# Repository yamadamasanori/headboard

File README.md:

# ヘッドボードLED コントローラ（ESP32-S3）

ベッドのヘッドボードに付けた LED を、Home Assistant から操作するための ESP32 ファームウェアと、ブラウザ用の書き込み・設定ページです。

- 読書灯とバックライトの 2 系統を、PWM でそれぞれ独立に調光（0〜255、なめらかにフェード）
- MQTT で Home Assistant から操作。MQTT 自動探索（discovery）に対応しているので、接続すると自動で「ライト」が 2 つ追加される。ブローカーには TLS（MQTTS）でも接続できる
- 量産向けに、USB では設定を変えられない。Wi-Fi はスマホから Bluetooth で、MQTT・Tailscale・GPIO などは Wi-Fi に繋がった本体の設定ページ（`http://headboard-xxxxxx.local/`）で設定する
- 本体の設定ページでは、動作ログ・前回の再起動の理由と直前のエラーも見られ、ファームウェアの更新（OTA）もできる。更新に失敗したら前の版に自動で戻る
- 最初のファームウェアの書き込みは、USB で繋いだパソコンのブラウザから行う（ESP Web Tools を同梱）
- 基板上のフルカラー LED で、Wi-Fi・Tailscale・MQTT の接続状態を色で表示。OLED ディスプレイ（SSD1306、128×64）をつなげば、文字でも表示（Seeed Studio XIAO ESP32S3 版は OLED で表示）
- Home Assistant から本体の状態（電波の強さ・再起動の理由・エラー・メモリ・温度など）と、ライトの点灯時間・消費電力・電力量を見られる。再起動やファームウェアの更新も Home Assistant から行える
- ESP32 自身が Tailscale で tailnet に参加し、離れた場所の Home Assistant の MQTT ブローカーにも VPN 経由で接続できる（[MicroLink](https://github.com/CamM2325/microlink) を組み込み）

## ファイル構成

| パス | 内容 |
|---|---|
| `main/` | ファームウェアのソース（ESP-IDF / C） |
| `main/Kconfig.projbuild` | ビルド時の設定（ボード、開発用に USB から設定できるようにするか、Home Assistant からの更新に使う配布元の URL） |
| `main/board.h` | ボードごとの違い（GPIO の既定値、配布するファイル名など） |
| `main/status_led.c`、`main/status_oled.c` | 状態表示（N16R8 のフルカラー LED、OLED）。表示する状態の判定は `main/status.c` で共通 |
| `main/oled_font.c` | OLED 用のフォント（X11 misc-fixed、パブリックドメイン。`tools/gen_font.py` で作る） |
| `components/mdns/` | mDNS（Espressif、Apache-2.0、mdns-v1.15.1 を同梱。`headboard-xxxxxx.local` の名前で本体を開くため） |
| `partitions.csv` | フラッシュの区画（N16R8 用。ファームウェア 4MB × 2 の OTA 構成と、クラッシュの記録 256KB） |
| `partitions_8mb.csv` | フラッシュ 8MB 用の区画（XIAO 用。ファームウェア 3.75MB × 2 と、クラッシュの記録 256KB） |
| `components/microlink/` | Tailscale クライアント MicroLink（MIT、コミット 1cb8d1c を同梱。中継（DERP）の地域が違う相手に送る変更あり、`VERSION` 参照） |
| `sdkconfig.defaults*` | ビルド設定（共通 / ESP32-S3 用 / ボードごと（`.n16r8`、`.xiao`）） |
| `keys/headboard-signing-pubkey.pem` | ファームウェアの署名を確かめる公開鍵（秘密鍵はリポジトリに入れない。「ファームウェアの署名」参照） |
| `web/index.html` | 書き込み・設定ページ。本体にも組み込まれ、本体の設定ページとしても使われる |
| `web/firmware/headboard-led-ota.bin` | ビルド済みファームウェア（ESP32-S3 用のアプリ。USB での書き込みと、本体の設定ページからの更新の両方に使う） |
| `web/firmware/headboard-led-boot.bin`, `headboard-led-otadata.bin` | USB で書き込むときに一緒に書き込むブートローダーとパーティション表、起動するアプリの選択（設定の保存領域には書き込まない） |
| `web/manifest.json` | ESP Web Tools 用の定義 |
| `web/xiao/` | XIAO ESP32S3 用の `manifest.json` と `firmware/headboard-led-xiao-*.bin`（ファイルの役割は N16R8 用と同じ） |
| `web/vendor/esp-web-tools/` | ESP Web Tools 10.4.0（Apache-2.0）。CDN に頼らずオフラインでも動くよう同梱 |
| `web/vendor/qrcode-generator/` | QR Code Generator 2.0.4（MIT）。本体ラベルの QR コード用 |
| `tools/serve.py` | 設定ページをローカルで開くための簡易サーバー |
| `.devcontainer/` | VS Code の devcontainer 設定（ESP-IDF v5.3.1 のイメージを使用） |
| `tools/build.sh` | ESP-IDF 環境でビルド・署名して `web/` を更新（docker は使わない。署名用の秘密鍵が必要） |
| `tools/package_web.py` | ビルド結果を `web/firmware/`（XIAO 用は `web/xiao/firmware/`）にまとめ、ライセンス表示を `web/` にコピーする |
| `tools/gen_font.py` | OLED 用のフォントを BDF から C の配列にする |
| `.github/workflows/pages.yml` | GitHub に置いた場合に、`web/` を GitHub Pages に公開する設定（ビルドはせず、ファームウェアの署名を確かめてから公開） |
| `platformio.ini` | PlatformIO でビルドする場合の設定 |
| `LICENSE` | このプロジェクトのライセンス（MIT） |
| `THIRD_PARTY_NOTICES.md` | 同梱・組み込みしている第三者のソフトウェアのライセンス |
| `web/LICENSE.txt`、`web/THIRD_PARTY_NOTICES.txt` | 上の 2 つのコピー（設定ページからリンク。`tools/package_web.py` が作成） |

## 基板と配線（既定値）

次の 2 種類のボードに対応しています。ファームウェアはボードごとに別です（書き込みページでボードを選びます）。

- ESP32-S3-DevKitC-1 互換の ESP32-S3 N16R8 基板（フラッシュ 16MB、オクタル PSRAM 8MB）。状態表示は基板上のフルカラー LED
- Seeed Studio XIAO ESP32S3（フラッシュ 8MB、オクタル PSRAM 8MB）。状態表示は、つないだ OLED ディスプレイ（SSD1306、128×64、I2C）。フラッシュ 16MB の XIAO ESP32S3 Plus でも、XIAO 用のファームウェアが動きます（8MB だけを使います）

### ESP32-S3 N16R8

| 用途 | 既定の GPIO |
|---|---|
| 読書灯 | GPIO4 |
| バックライト | GPIO5 |
| 状態表示 LED（基板上の WS2812） | GPIO48 |
| OLED の SDA・SCL（任意） | 使わない（つなぐときの例: GPIO8・GPIO9） |

OLED ディスプレイ（SSD1306）もつなげます。3.3V・GND・SCL・SDA の 4 本でつなぎ、設定ページの「状態表示」で SDA と SCL の GPIO を入れて保存します。フルカラー LED と OLED の両方に表示します（表示の内容は「[状態表示（OLED）](#状態表示oled)」）。起動時の動作に関わる GPIO0・3・45・46 と、使用中の GPIO48・4・5 は避けてください。

GPIO は設定ページから変更できます。フラッシュと PSRAM が使う GPIO26〜37、USB 端子の GPIO19・20、COM 端子の GPIO43・44 は選べません。
ESP32 のピンで LED を直接駆動することはできないので、ロジックレベル N チャネル MOSFET などのドライバを挟んでください。ドライバがアクティブ Low の回路なら、設定ページの「出力を反転する」をオンにします。PWM 周波数の既定は 5 kHz（13 bit 分解能。周波数を下げると最大 14 bit）です。

明るさ（1〜255）は、設定ページの「最小デューティ比」（明るさ 1）から「最大デューティ比」（明るさ 255）までを対数で割り振ります。1 段ごとに同じ割合で明るくなるので、目で見た変化がほぼ均等になります（照明の調光規格 DALI と同じ考え方。既定の 0.1〜100% では 1 段で約 2.8%、明るさ 50% で約 3%）。暗いときにちらつくなら最小を上げ、明るい側で変化がなくなるなら最大を下げて、回路に合わせてください。

LED 電球などに入っている定電流ドライバ（入力に電解コンデンサとコイルがある小さな基板）を、電源ごと PWM でオン・オフするつなぎ方は、調光に向きません。コンデンサで平らにされて明るい側で変化がなくなり、暗い側ではドライバが止まったり動いたりしてちらつきます。LED に直列に電流制限の抵抗を入れて MOSFET で駆動するか、PWM 調光の入力（DIM 端子）があるドライバを使ってください。

基板の USB-C 端子は 2 つとも使えます。

- **COM 端子**（USB シリアル変換チップ経由）: 書き込み・状態表示・ラベル表示ができ、動作ログも出ます
- **USB 端子**（ESP32-S3 内蔵の USB）: 書き込み・状態表示・ラベル表示ができます。ログは出ません

基板の BOOT ボタン（GPIO0）は、動作中に長押しすると次のように働きます。

| 押す長さ | 動作 | 状態表示 LED |
|---|---|---|
| 3 秒以上 | Wi-Fi の設定だけを消して再起動し、Bluetooth での設定を待つ（MQTT などの設定は残る）。「Tailscale からだけ受け付ける」もオフに戻す | 白・点灯 |
| 10 秒以上 | すべての設定と累計（点灯時間・起動回数など）を消して再起動（工場出荷時の状態） | 赤・点灯 |

LED の色が変わったところで離すと、その動作をします。短く押すと、消えている状態表示を 10 秒間出し直します。

### Seeed Studio XIAO ESP32S3

| 用途 | 既定の GPIO（XIAO のピン） |
|---|---|
| 読書灯（LED1） | GPIO7（D8） |
| バックライト（LED2・LED3） | GPIO44（D7） |
| OLED の SDA | GPIO8（D9） |
| OLED の SCL | GPIO9（D10） |

- OLED は 3.3V・GND・SCL・SDA の 4 本でつなぎます（I2C のアドレスは 0x3C か 0x3D を自動で探します）。OLED の GPIO は、設定ページで変えられます（両方 -1 で使わない）
- 既定の GPIO は専用基板の配線に合わせています
- XIAO の USB-C 端子は ESP32-S3 内蔵の USB です。書き込み・状態表示・ラベル表示ができます。ログは D6（GPIO43、TX）に出るので、見るときは USB シリアル変換器をつないでください（設定ページのログ欄は、本体の設定ページなら Wi-Fi 経由で見られます）
- D7（GPIO44）は COM 端子の RX ですが、XIAO ではバックライトに使うので、COM 端子からの設定の入力は受け付けません（設定は USB-C 端子から）
- D6（GPIO43）はログ用なので選べません。D2（GPIO3）は起動時の動作を決めるピンなので、ライトには使わないでください
- BOOT ボタン（B）の働きは N16R8 と同じです。押している間は、画面に離したときの動作と、押している秒数が出ます
- 基板上のオレンジの LED（GPIO21）は使いません

## 状態表示 LED

| 状態 | 色と光り方 |
|---|---|
| Wi-Fi 未設定（Bluetooth での設定待ち） | 紫・ゆっくり点滅 |
| Wi-Fi 接続中・切断 | 青・速い点滅 |
| Tailscale 接続中（Tailscale を使う場合） | 水色・点滅 |
| MQTT 接続待ち・切断、ブローカー未設定 | 黄・点滅 |
| Tailscale の認証失敗、MQTT の接続拒否（ユーザー名・パスワード違い） | 赤・点滅 |
| すべて正常 | 緑・点灯 → 10 秒後に消灯 |
| Home Assistant からの操作を受信 | 緑・一瞬点滅 |

- 起動直後に白が一瞬点灯します（LED の点灯確認）
- 問題が複数あるときは、Wi-Fi → Tailscale → MQTT の順に、先にある問題を表示します
- 明るさ（既定 32/255）、GPIO（-1 で使わない）、正常時も点灯し続けるかは、設定ページの「状態表示 LED」で変えられます。いま表示している状態は「動作確認」欄にも出ます
- 互換基板には、LED の横に「RGB」と書かれたはんだジャンパがあり、そこをはんだで繋がないと点灯しない製品があります。点灯しないときは確認してください

## 状態表示（OLED）

XIAO ESP32S3 では標準の表示です。N16R8 では、つないで設定したときだけ表示します（フルカラー LED と両方に表示）。

上段（16 ドット）にホスト名と接続状態のアイコン、下段に 1 行 16 文字 × 3 行で状態を英語で表示します。上段の高さを 16 ドットにしているので、上が黄色・下が青の 2 色のモジュールでも、区切りが合います。

```
headboard-a1b2c3  ▂▄▆ [TS][MQ]     ← Wi-Fi の電波の強さ、Tailscale、MQTT
Reading   ON  80%
Backlight OFF
192.168.1.23                        ← Tailscale を使っていれば、tailnet の IP と 3 秒ごとに交互
```

| 状態 | 表示 |
|---|---|
| 起動直後（1 秒） | `Headboard LED`、版、`XIAO ESP32S3` |
| Bluetooth での設定待ち | `Wi-Fi not set` / `Setup via BLE:` / 本体の名前（`PROV_HB_xxxxxx`）。設定用コードは表示しません |
| Wi-Fi 接続中・切断 | `Wi-Fi` / `Connecting...` / SSID |
| Tailscale の認証失敗 | `Tailscale` / `Auth failed (!)` / `Check auth key` |
| Tailscale 接続中 | `Tailscale` / `Connecting...` |
| MQTT の接続拒否 | `MQTT` / `Refused (!)` / `Check user/pass` |
| ブローカー未設定 | `MQTT` / `Not configured` / `Open web setup` |
| MQTT 接続中・切断 | `MQTT` / `Connecting...` / ブローカーのホスト名 |
| すべて正常 | ライトの状態と IP アドレス → 10 秒後に画面を消す |
| BOOT ボタンを押している | `3s: Reset Wi-Fi` / `10s: Reset all` と進み具合 → 3 秒で `Release to: Reset Wi-Fi` → 10 秒で画面全体を反転して `Release to: RESET ALL` |
| 本体を光らせる（Home Assistant） | 画面全体を速く点滅し、`HERE` を大きく表示（10 秒） |

- 上段のアイコンは、繋がっていれば塗りつぶし、接続中は枠だけ、エラーは斜線入りです。Tailscale を使わないときは TS を出しません。下段に tailnet の IP を出している間は、TS の下に線が出ます
- 画面が消えているときも、Home Assistant からライトを操作すると 5 秒（操作したライトの行を 1 秒反転）、BOOT ボタンを短く押すと 10 秒表示します。問題があるときは、消さずに表示し続けます
- 明るさ（既定 32/255）と、正常なときも表示し続けるか、表示を 180° 回すかは、設定ページの「状態表示」で変えられます。明るさは Home Assistant からも変えられ、すぐに反映されます。明るさが 32 未満のときは、OLED の駆動の設定（プリチャージ期間と VCOMH の電圧）を段階的に下げて、さらに暗くします
- 焼き付きを防ぐため、表示を 1 分ごとに 0〜2 ドット横にずらします

## 使い方

量産時の流れは次のとおりです。USB を使うのは 1 の書き込みとラベルの印刷だけで、設定はすべて無線で行います。

1. 未設定のファームウェアを USB で書き込み、本体のラベル（QR コードと設定用コード）を印刷して貼る
2. スマホのアプリ「ESP BLE Provisioning」で QR コードを読み、Wi-Fi を設定する
3. 同じネットワークのパソコンかスマホで本体の設定ページを開き、MQTT などを設定する

### 1. ファームウェアを書き込む（USB）

Web Serial は HTTPS か localhost でしか動かないため、HTML ファイルを直接開かずに、次のどちらかで書き込み用のページを開きます。

- devcontainer の中で `python tools/serve.py` を実行し（8000 番は自動で転送されます）、ホストの Chrome か Edge で http://localhost:8000 を開く
- GitHub のリポジトリに置き、GitHub Pages を有効にする（`.github/workflows/pages.yml` が `web/` を自動で公開します）

基板を USB で繋ぎ、ボード（ESP32-S3 N16R8 か Seeed Studio XIAO ESP32S3）を選んでから「ESP32 に書き込む」を押してシリアルポートを選びます。初回は「消去」を選んでください。
ボードを間違えて N16R8 用を XIAO に書き込むと、「ESP32 に接続」したときに警告が出ます（フラッシュの大きさで判断します）。
COM 端子でポートが表示されないときは、USB シリアル変換チップ（CH340 / CH343 / CP210x）のドライバを入れてください。書き込みが始まらないときは、BOOT ボタンを押したまま RST ボタンを押して離し、書き込みモードにしてから試してください。

2.4.0 からは、USB で書き込んでも設定は消えません（「消去」を選んだときだけ消えます）。2.3.0 までは、USB で書き込むと「消去」を選ばなくても設定が消えていました。

**2.0.0 より前の版から上げるとき:** フラッシュの区画を OTA 用に変えたため、一度だけ USB で「消去」を選んで書き込んでください。それまでの設定は消えるので、設定し直しが必要です。2.0.0 以降は、本体の設定ページから更新できます。

### 2. ラベルを印刷する（USB）

書き込み画面を閉じてから「ESP32 に接続」を押すと、本体の名前（`PROV_HB_xxxxxx`）、設定用コード（8 文字）、本体の設定ページのアドレスと、アプリ用の QR コードが表示されます。「ラベルを印刷」で、この部分だけを印刷できます。

- 設定用コードは本体ごとに決まっていて（チップ固有の ID から作る）、Bluetooth での設定と本体の設定ページのログインに使います。他の人に見せないでください
- ごくまれに固有 ID の無いチップがあり、その場合は初回の起動時に乱数でコードを作って保存します。この場合だけは、工場出荷時に戻してもコードは変わりませんが、フラッシュを消去して書き込むとコードが変わるので、ラベルを貼り直してください
- 量産版のファームウェアは USB から設定を変えられないため、USB の画面には設定の欄が出ません（「状態」「ログ」「点灯テスト」は使えます）

### 3. Wi-Fi を設定する（Bluetooth）

1. スマホに Espressif の公式アプリ「ESP BLE Provisioning」（iOS / Android）を入れます
2. 本体の電源を入れ、状態表示 LED が紫でゆっくり点滅していることを確かめます（Bluetooth での設定待ち）
3. アプリで「Provision New Device」を選び、ラベルの QR コードを読みます。QR が使えないときは、手動で本体の名前（`PROV_HB_xxxxxx`）を選び、設定用コードを入れます
4. 一覧から Wi-Fi を選び、パスワードを入れます。繋がると設定が保存され、Bluetooth は止まります

パスワードの誤りなどで繋がらないときは、アプリにその旨が表示され、そのまま入れ直せます。Wi-Fi を変えたいときは、BOOT ボタンを 3 秒以上押してください。

### 4. 本体の設定ページで設定する（Wi-Fi）

本体と同じネットワークのパソコンかスマホのブラウザで `http://headboard-xxxxxx.local/` を開き（`xxxxxx` はラベルに書かれています）、設定用コードでログインします。`.local` の名前で開けないとき（一部の Android など）は、ルーターの管理画面で本体の IP アドレスを調べて `http://<IP アドレス>/` で開いてください。

MQTT ブローカー（Home Assistant の Mosquitto アドオンなど）のアドレス・ユーザー名・パスワードなどを入力して「保存して再起動」を押します。
パスワード欄は、空欄のまま保存すると以前の値が残ります。「動作確認」のスライダーで、その場で明るさを変えられます。

#### MQTT を TLS で接続する（任意）

ブローカーが TLS（MQTTS、通常は 8883 番）に対応していれば、「MQTT」欄の「TLS で接続する」をオンにします（ポートが 1883 なら 8883 に変わります）。

- ブローカーの証明書を自分で作った（自前の CA で署名した）場合は、「CA 証明書」に CA の証明書（`ca.crt` など、`-----BEGIN CERTIFICATE-----` で始まるもの）の中身を貼り付けます。空欄なら、公開の認証局（Let's Encrypt など）の証明書として確かめます
- 「ブローカーのホスト名 / IP」は、ブローカーの証明書に入っている名前か IP アドレス（subjectAltName）のどれかと同じにしてください。違うと接続しません
- 本体は時計を持たないので、証明書の有効期限は確かめません（期限が切れても繋がります）。期限の前に作り直してください
- Tailscale 経由の接続はもともと暗号化されていますが、TLS をオンにすれば、その場合も同じように証明書を確かめます

- この設定ページは暗号化していない HTTP です。家庭内の LAN で使う前提です（Tailscale 経由で開けば、経路は暗号化されます。Tailscale からだけ開けるようにもできます。「5. Tailscale を使う」参照）
- 設定用コードを 5 回続けて間違えると、1 分間ログインできなくなります

#### ファームウェアの更新（OTA）

本体の設定ページの「ファームウェアの更新」で `web/firmware/headboard-led-ota.bin`（XIAO は `web/xiao/firmware/headboard-led-xiao-ota.bin`）を選んで「更新する」を押します。書き込みが終わると再起動します。

- 新しいファームウェアが起動して Wi-Fi に繋がるまで（Wi-Fi 未設定なら起動するまで）に失敗すると、次の起動で前の版に自動で戻ります
- `headboard-led-boot.bin` などの USB 用のファイルや ESP32-S3 用でないファイル、別のボード用のファイルは、書き込む前に断ります（ボードごとにプロジェクト名を変えて見分けています。2.5.0 以前の N16R8 も、XIAO 用は断ります）
- 2.3.0 からは、正しい鍵で署名したファームウェアだけを書き込みます（Home Assistant からの更新も同じ）。署名がないものや違う鍵のものは、書き込みの最後で断り、今の版のまま動き続けます。2.2.0 以前から 2.3.0 への更新は、まだ署名を確かめない版からなので、そのまま入ります

Home Assistant の「設定 → 更新」からも更新できます（下の「6. Home Assistant で確認する」）。

#### 開発用に USB から設定できるようにする

開発中は、`idf.py menuconfig` の「ヘッドボードLED → USB から設定を変更できるようにする（開発用）」をオンにしてビルドすると、以前の版と同じように USB の設定ページから Wi-Fi・MQTT などを設定できます。量産用のファームウェアでは必ずオフ（既定）にしてください。

### ログの見方と MQTT に繋がらないとき

本体の設定ページ（USB の設定ページでも同じ）の「動作確認」欄は自動で更新され、MQTT に繋がっていないときは、その理由が赤字で表示されます。起動してからの時間、前回の再起動の理由（電源投入・クラッシュ・ウォッチドッグなど）、空きメモリ（内蔵 RAM の今と起動してからの最小値、PSRAM）、直近のエラーと、前回の起動中の最後のエラーも表示されます。

前回の起動がクラッシュで終わったときは、「前回のクラッシュ」にクラッシュの理由・タスク・Backtrace（アドレスの並び）が赤字で表示されます。クラッシュの記録をフラッシュに残しておき、次の起動で読み出すので、シリアルを繋いでいなくても分かります。アドレスは、同じ版をビルドした `build/headboard_led.elf` で関数と行に変換できます（`xtensa-esp32s3-elf-addr2line -pfiaC -e build/headboard_led.elf <アドレス…>`）。

- クラッシュの記録の区画は 2.4.0 で追加しました。2.3.0 以前から本体の設定ページ（Wi-Fi）で更新した本体には区画がないので、一度 USB で書き込んでください（2.4.0 の書き込みページからなら設定は消えません）

| 表示 | 主な原因 |
|---|---|
| 接続を拒否されました: ユーザー名かパスワードが違います / 認証されませんでした | MQTT のユーザー名・パスワード（Home Assistant の Mosquitto アドオンなら、HA のユーザーか、アドオン設定の logins） |
| 接続を断られました / 接続が切られました | ポート番号の誤り（通常は 1883、TLS なら 8883）、ブローカーが動いていない |
| TLS で接続できません | TLS 用でないポート（1883 など）に TLS で繋ごうとしている |
| ブローカーの証明書に「…」が入っていません | ブローカーのホスト名 / IP が、証明書に入っている名前・IP と違う |
| ブローカーの証明書が、設定した CA 証明書で確かめられません | 貼り付けた CA 証明書が、ブローカーの証明書に署名した CA のものでない |
| 応答がありません | IP アドレスの誤り、ファイアウォール、別のネットワーク |
| ホスト名を IP アドレスに変換できません | `homeassistant.local` のような名前は使えないことがあります。IP アドレスで指定してください |
| Tailscale の接続を待っています | Tailscale がオンで、ブローカーにホスト名か tailnet のアドレス（100.64〜100.127）を指定していて、Tailscale がまだ繋がっていない |

ログ欄には次の機能があります。本体の設定ページでは、本体が貯めている起動してからのログ（最大 64KB）を、Wi-Fi 経由でいつでも見られます。USB では COM 端子で接続したときだけ表示されます。前回の起動の最後のログ（2KB、クラッシュの直前など）は「[前回]」を付けて最初に表示します。電源を切ると前回のログは消えます。

- 「一時停止」: 表示を止めます（受信は続き、「再開」でまとめて表示）。ログ欄を上にスクロールしても止まります
- 「直近500行をコピー」: 絞り込み後の最新 500 行をクリップボードにコピーします
- 「ファイルに保存」: 受信した全ログ（最大 20,000 行）をテキストファイルに保存します
- 絞り込み欄（例: `mqtt`、`broker:`）と「警告とエラーだけ」。エラーは赤、警告は黄で表示されます

Tailscale の途中経過のログは、通常は警告以上だけにしています。調べたいときは「デバイス」欄の「詳細ログを出す」をオンにして保存してください。

### 5. Tailscale を使う（任意）

1. Tailscale の管理画面（Settings → Keys）で認証キーを作ります。ESP32 を置きっぱなしにするなら「Reusable」はオフ、期限切れで外れないよう登録後にデバイスの「Disable key expiry」をオンにしておくと安心です
2. 本体の設定ページの「Tailscale」で「tailnet に接続する」をオンにし、認証キーと tailnet 上のホスト名（既定は `headboard-xxxxxx`）を入れて保存します
3. MQTT ブローカーのホスト名に、Home Assistant の tailnet 上の名前（例: `homeassistant`）か tailnet のアドレス（`100.64.x.x`〜`100.127.x.x`）を入れると、Tailscale 経由で接続します。LAN の IP アドレスを入れた場合は、Tailscale の接続を待たずに LAN で直接繋ぎます。`homeassistant.local` のような LAN のホスト名も、Tailscale がオンのときは Tailscale の接続を待ってから繋ぎます（tailnet 上に同じ名前が無ければ、通常の DNS で探します）

「動作確認」欄に Tailscale の状態と VPN の IP アドレスが表示されます。認証キーかホスト名を変えると、次の起動時に鍵を作り直して登録し直します。

#### 本体の設定ページを Tailscale からだけ開けるようにする（任意）

「Tailscale」欄の「本体の設定ページと更新を Tailscale からだけ受け付ける」をオンにすると、LAN から本体の設定ページ・WebSocket・ファームウェアの更新に繋いでも断ります（「Tailscale からだけ開けます」と表示）。設定用コードが漏れても、LAN 内からは設定も更新もできなくなります。

- 先に、Tailscale で `http://<tailnet 上のホスト名>/` を開けることを確かめてからオンにしてください（オンにするときに確認が出ます）
- Tailscale の ACL で、本体に繋げる端末を自分の端末と Home Assistant に絞っておくと、さらに安全です
- tailnet から本体の tailnet の IP に繋いできた接続だけを受け付けます。接続元のアドレスだけでは判断しないので、LAN から接続元を偽っても開けません。2.4.1 からの動作です
- Tailscale に繋がらなくなると、本体の設定ページは開けません（ライト・MQTT・Home Assistant からの更新はそのまま動きます）。戻すには、BOOT ボタンを 3 秒押して Wi-Fi の設定を消し、Bluetooth で設定し直します。これで LAN からも開けるようになります
- Home Assistant のデバイスのページの「デバイスを設定」のリンクは、いつも `http://headboard-xxxxxx.local/`（LAN）を指すので、オンのときは「Tailscale からだけ開けます」と表示されます。Tailscale の `http://<tailnet 上のホスト名>/` から開いてください
- Home Assistant からの更新（GitHub Pages から本体が取りに行く）と、MQTT の接続には関係しません。MQTT も Tailscale 経由にしたいときは、ブローカーに tailnet の名前かアドレスを指定します

### 6. Home Assistant で確認する

Home Assistant に MQTT 統合が設定されていれば、「設定 → デバイスとサービス → MQTT」に、設定ページで付けた名前のデバイスが現れ、「読書灯」と「バックライト」の 2 つのライトが追加されます。明るさとフェード時間（transition）を指定できます。

デバイスのページには、ライトのほかに次のエンティティが追加されます。診断と操作の項目は、デバイスのページの「診断」「設定」欄にまとまり、普段のダッシュボードには出ません。

| 種類 | エンティティ |
|---|---|
| ライトの累計 | 読書灯・バックライトそれぞれの点灯時間、点灯回数、消費電力（推定）、電力量（推定） |
| 診断 | Wi-Fi の電波の強さ・SSID・アクセスポイント・チャンネル、IP アドレス、稼働時間、前回の再起動の理由、前回の再起動が異常か（電圧低下・クラッシュ・ウォッチドッグ）、直前のエラー、前回の起動の最後のエラー、空きメモリ（今と最小値）、内蔵 RAM の空き（今と最小値）、PSRAM の空き、チップの温度、状態表示 LED の表示、起動した回数、電圧低下による再起動の回数、クラッシュによる再起動の回数、Wi-Fi が切れた回数、MQTT の再接続の回数 |
| 診断（Tailscale を使うときだけ） | Tailscale の状態・IP アドレス・ピアの数・認証エラー |
| 操作 | 再起動、本体を光らせる（状態表示 LED が白で 10 秒速く点滅。XIAO は画面が点滅）、更新を確認（配布元の新しい版をすぐに確かめる。配布元を設定したときだけ）、累計をクリア（設定は残る。誤操作を避けるため最初は無効で、使うときはデバイスのページで有効にする）、状態表示 LED の明るさ、状態表示 LED を常に点灯、詳細ログ（XIAO では「画面の明るさ」「画面を常に表示」） |
| 更新 | ファームウェア（新しい版があると「設定 → 更新」に出て、そこから書き込める） |

- 値は 60 秒ごと（と、操作したとき・MQTT に繋がったとき）に送ります
- 消費電力と電力量は、本体の設定ページの「定格消費電力」（既定 1 W）× PWM のデューティ比から計算した推定値です。電力量は Home Assistant の「エネルギー」ダッシュボードに個別のデバイスとして追加できます
- 点灯時間・点灯回数・電力量・起動回数などの累計は、本体に 10 分ごと（と意図した再起動の前）に保存し、再起動しても続きから数えます。電源を急に切ると、最後の保存から後の分（最大 10 分）は残りません
- 累計は工場出荷時に戻すか、設定ページか Home Assistant の「累計をクリア」で 0 に戻ります（「累計をクリア」では設定は残ります）。量産時の検査で増えた分は、出荷前に消してください
- Wi-Fi が切れた回数と MQTT の再接続の回数は、起動してからの回数です（Home Assistant の履歴で長期の傾向を見られます）
- 新しい版は、本体が MQTT につないだときと 6 時間ごと（と HA の「更新を確認」ボタンを押したとき）に配布元（既定は `https://yamadamasanori.github.io/headboard/`、XIAO は `https://yamadamasanori.github.io/headboard/xiao/`。`idf.py menuconfig` の「ヘッドボードLED → ファームウェアの配布元」で変更、空にすると使わない）の `manifest.json` を見て探します。HTTPS でサーバーの証明書を確かめてから取得します。GitHub に push してから Pages に公開され、キャッシュが切れるまで 10 分ほどかかります
- 設定用コード・パスワード・Tailscale の認証キーは MQTT に送りません

## MQTT の仕様

`<id>` は MAC アドレスから作る固有 ID（例: `headboard_a1b2c3`）で、設定ページに表示されます。

| トピック | 向き | 内容 |
|---|---|---|
| `homeassistant/light/<id>/reading/config` など | ESP32 → HA | 自動探索の設定（retain） |
| `headboard/<id>/status` | ESP32 → HA | `online` / `offline`（LWT、retain） |
| `headboard/<id>/reading/set`、`.../backlight/set` | HA → ESP32 | `{"state":"ON","brightness":128,"transition":2}`。`ON` / `OFF` だけでも可 |
| `headboard/<id>/reading/state`、`.../backlight/state` | ESP32 → HA | `{"state":"ON","brightness":128,"color_mode":"brightness"}`（retain） |
| `homeassistant/<sensor など>/<id>/<key>/config` | ESP32 → HA | 診断・累計・操作・更新のエンティティの自動探索の設定（retain）。使わなくなったもの（Tailscale をオフにしたときなど）は空のメッセージで消す |
| `headboard/<id>/diag` | ESP32 → HA | 診断と累計をまとめた JSON（60 秒ごと、retain）。各エンティティは `value_template` でここから値を取り出す |
| `headboard/<id>/update` | ESP32 → HA | `{"installed_version":"2.1.1","latest_version":"2.1.2","release_url":"https://github.com/yamadamasanori/headboard/releases/tag/v2.1.2","in_progress":false,"update_percentage":null}`（retain）。`release_url` は HA の「リリースのお知らせを読む」のリンク |
| `headboard/<id>/restart/set`、`.../identify/set`、`.../check_update/set`、`.../reset_usage/set` | HA → ESP32 | ボタン（内容は何でもよい）。retain 付きのものは無視する |
| `headboard/<id>/sled_brightness/set` | HA → ESP32 | `1`〜`255` |
| `headboard/<id>/sled_always_on/set`、`.../log_verbose/set` | HA → ESP32 | `ON` / `OFF`（本体に保存し、すぐに反映） |
| `headboard/<id>/update/set` | HA → ESP32 | `install` で配布元の新しい版を書き込んで再起動。retain 付きのものは無視する |

ボタンと更新のコマンドは、ブローカーに保持（retain）されていると繋ぐたびに届き、再起動や更新を繰り返してしまうので、retain 付きのものは無視します（ログに `ignored retained command` と出ます）。

Home Assistant が再起動したとき（`homeassistant/status` に `online`）は、自動探索の設定を送り直します。電源投入時はどちらも消灯から始まります。

## 設定コマンド（USB シリアルと WebSocket）

設定ページは、115200 bps のシリアル（USB）か、本体の `ws://headboard-xxxxxx.local/ws`（Wi-Fi）で、1 行 1 コマンドの JSON を送っています。応答は `@@` で始まる 1 行の JSON です（それ以外の行はログ）。WebSocket では最初に `{"cmd":"login","pop":"<設定用コード>"}` でログインします。

```
{"cmd":"hello"}                      機種・バージョン・本体の名前（USB では設定用コードも）
{"cmd":"get"}                        現在の設定（パスワードは「設定済みか」だけ）
{"cmd":"set","config":{...},"reboot":true}   設定を保存（含めた項目だけ変更）
{"cmd":"status"}                     Wi-Fi / MQTT / Tailscale / ライト / 状態表示 LED の状態、空きメモリ（合計・内蔵 RAM の今と最小値・PSRAM）、再起動の理由、エラー、前回のクラッシュ
{"cmd":"prev_log"}                   前回の起動の最後のログ
{"cmd":"light","id":"reading","brightness":100}   点灯テスト
{"cmd":"reset_usage"}                累計（起動回数・点灯時間・電力量など）を 0 に戻す（設定は残す）
{"cmd":"reboot"} / {"cmd":"factory_reset"}
```

量産版（開発用の設定がオフ）では、USB から使えるのは `hello`・`status`・`light`・`prev_log` だけです。

## ビルド

VS Code で「Reopen in Container」を選び、コンテナの中で次を実行します。ESP-IDF v5.3.1 と Python はイメージに入っているので、ホストに ESP-IDF や Python は不要です。docker コマンドは使いません。

```sh
sh tools/build.sh
```

N16R8 用と XIAO 用の両方をビルドし、`web/firmware/`（アプリの `headboard-led-ota.bin` と、USB 用の `headboard-led-boot.bin`・`headboard-led-otadata.bin`）と `web/manifest.json`、`web/xiao/`（同じく `headboard-led-xiao-*.bin` と `manifest.json`）も更新されます。署名用の秘密鍵（`secrets/headboard-signing-key.pem`）がないとビルドできません。`build.sh` は `idf.py set-target` で `sdkconfig`（XIAO は `sdkconfig.xiao`）を作り直すので、`menuconfig` で開発用の設定をオンにしたときは、`build.sh` ではなく次のように実行してください。

```sh
idf.py build && python tools/package_web.py                                    # N16R8
idf.py -B build-xiao -DHB_BOARD=xiao build && python tools/package_web.py build-xiao   # XIAO
```

ボードは `-DHB_BOARD`（既定は `n16r8`）で選びます。ボードごとに `sdkconfig` とビルドのディレクトリを分けてください（XIAO は `sdkconfig.xiao` と `build-xiao`）。混ざるとビルドが止まります。

PlatformIO（`platformio.ini`）の設定は残していますが、動作確認をしていない補助的な経路です。

### ファームウェアの署名

ファームウェアは RSA-3072 の鍵で署名しています（ESP-IDF の「Secure Boot なしの署名付きアプリ」。eFuse は書き込まないので元に戻せます）。本体は無線での更新（本体の設定ページ・Home Assistant）のときに、今動いている版と同じ鍵で署名されているかを確かめ、違えば書き込みません。設定用コードが漏れても、配布元（GitHub）が乗っ取られても、偽のファームウェアは入りません。

- 秘密鍵は `secrets/headboard-signing-key.pem`（`.gitignore` 済み）。**リポジトリにも GitHub にも置かず、別の場所（パスワードマネージャー、暗号化した USB メモリなど）にバックアップしてください**
- 秘密鍵をなくすと、出荷済みの本体を無線で更新できなくなります（USB で書き直せば、新しい鍵の版に移れます）
- 秘密鍵が漏れたら、新しい鍵を作り、すべての本体を USB で書き直してください
- 公開鍵は `keys/headboard-signing-pubkey.pem`。GitHub Actions は、公開する前にこの公開鍵で `web/firmware/headboard-led-ota.bin` の署名を確かめ、合わなければ公開しません（ファームウェアは手元でビルド・署名してコミットする）
- USB での書き込みは今までどおりで、署名は確かめません（本体に触れられる人からの書き換えは防げません。防ぐには Secure Boot v2 が必要で、eFuse を書くので元に戻せません）

鍵を作り直すとき（ESP-IDF の環境で）:

```sh
espsecure.py generate_signing_key --version 2 --scheme rsa3072 secrets/headboard-signing-key.pem
espsecure.py extract_public_key --version 2 --keyfile secrets/headboard-signing-key.pem keys/headboard-signing-pubkey.pem
```

ファームウェアを ESP-IDF で作ったのは、Tailscale を ESP32 上で動かす唯一の選択肢（MicroLink）が ESP-IDF 専用だからです。Arduino では組み込めません。

## 動作確認したこと

- 2.6.0（XIAO ESP32S3 対応、N16R8 への OLED の追加）は、ESP-IDF v5.3.1 で N16R8 用・XIAO 用の両方のビルドが通ること、XIAO 用のパーティション表とフラッシュの大きさ（8MB）、署名を確認しました。OLED の各画面は、描画の処理をパソコン上で動かして画像にして確認しました。N16R8 に OLED（GME-12864-52、SSD1306）をつないだ実機で、OTA での更新、I2C での表示、明るさの効き方（1〜31 の段階的な減光を含む）、180° 回転、BOOT ボタンの案内と短く押したときの再表示、正常になってから 10 秒で画面を消すこと、Home Assistant からライトを操作したときの 5 秒の表示を確認しました。XIAO の実機ではまだ確かめていません（Wi-Fi・Bluetooth、8MB のパーティションでの起動と OTA）
- 2.6.1 は、N16R8 に OLED をつないだ実機で、電源を入れた直後から表示されること、動作中に OLED の線を外してつなぎ直すと表示が戻ることを確認しました
- 2.7.0 は、N16R8 の実機で、中継の地域が本体（東京、7）と違う相手（米国のサーバー上の Home Assistant、シアトル、10）に、追加の中継の接続を通して tailnet 経由で MQTT に接続できること（tailnet につながってから約 35 秒）、TLS の作業領域を PSRAM に移して内蔵 RAM の空きが約 31KB から 47KB（最小 37KB）に増えたこと、mDNS 1.15.1 で `http://headboard-xxxxxx.local/` が開くことを確認しました
- 2.7.1（XIAO の既定の GPIO を専用基板に合わせる）は、N16R8 用・XIAO 用の両方のビルドが通ることと署名を確認しました。XIAO の実機ではまだ確かめていません
- 2.8.0（調光カーブを対数にし、最小・最大のデューティ比を設定できるようにする）は、N16R8 用・XIAO 用の両方のビルドが通ることと署名を確認しました。実機ではまだ確かめていません
- 2.9.0（MicroLink を本家の 1cb8d1c に更新し、中継の地域が違う相手に送る変更を当て直す。tailnet の ACL を本体でも守る）は、XIAO の実機で、tailnet の ACL を本体でも守るようになっても設定ページと MQTT が使えること、更新したあと元のファームウェアに戻らないことを確認しました。このときブローカー（Google Cloud 上のサーバー）とは中継なしで直接つながっていたため、地域が違う中継を通して送る動作は 2.9.0 ではまだ確かめていません
- ESP-IDF v5.3.1 で、ESP32-S3 向けのビルドが通ることを確認しました
- ESP32-S3 のエミュレータ（QEMU、Wi-Fi の代わりに仮想の有線 LAN）上で起動し、本体の設定ページを Chromium で開いて、次を確認しました
  - 設定用コードでのログイン（誤ったコードの拒否）、設定の読み込みと保存、再起動後の自動再接続
  - ログの表示（起動時のログを含む、再接続しても重複しない）、前回の起動のエラーの表示、明るさのスライダー
  - ファームウェアの更新で、ESP32 用でないファイルと一体型イメージを書き込む前に断ること、書き込みの進み具合の表示
- 以前の版で、MQTT の自動探索・状態送信・コマンドでの点灯、Tailscale を有効にしたときの起動、状態表示 LED の切り替えもエミュレータで確認済みです
- 2.1.0 の Home Assistant 連携を、エミュレータと MQTT ブローカーで次のように確認しました
  - 自動探索の設定 40 件がすべて正しい JSON で届くこと、Tailscale を使わないときに Tailscale の 4 件を消すこと
  - 診断情報の送信（60 秒ごと）、ライトの点灯で点灯回数・点灯時間・消費電力・電力量が計算どおりに増えること（1 W・明るさ 255 で 32 秒 → 0.0089 Wh など）
  - 状態表示 LED の明るさ・常時点灯・詳細ログの切り替え、本体を光らせるボタン、再起動ボタン（再起動の理由が「ソフトウェアによる再起動」になる）
  - ブローカーが止まって戻ったときに、再接続の回数が増え、直前のエラーに記録されること
  - 配布元の確認（GitHub Pages に HTTPS で接続し、証明書の確認が通ること）、新しい版の検出、Home Assistant からの更新の開始と進み具合（10% ごと）の送信、失敗したときに元の版のまま動き続けること

実機での確認はまだです。2.1.0 の Home Assistant 連携では、特に次を実機で確かめてください。エミュレータでは確認できませんでした。

- 再起動をまたいで累計と、Home Assistant から変えた設定が残ること（エミュレータではフラッシュへの書き込みが残らないため）
- チップの温度（エミュレータは温度センサーを再現できず、読み取りで止まるため外して試験しました）
- Wi-Fi の電波の強さ・SSID・アクセスポイント・チャンネル（エミュレータは有線 LAN のため）
- Home Assistant からの更新の完了（書き込みの最後の検証まで）。配布元の GitHub Pages を公開してから試してください
- 電源を抜き差しして電圧低下の回数が増えないこと、電源が弱いときに増えること

ほかに、Bluetooth での Wi-Fi 設定（エミュレータは Bluetooth を再現できません）、ファームウェアの更新の完了と自動で前の版に戻ること（エミュレータではフラッシュへの書き込みが残らないため、最後の検証で失敗します）、BOOT ボタンの長押し、`.local` の名前での接続は、実機で確かめる必要があります。LED の実際の色と点灯、PWM での点灯、Wi-Fi 接続、Tailscale への実際の登録と接続、PlatformIO でのビルドも未確認です。

## Tailscale について

ESP32 で動く Tailscale クライアントは、コミュニティ製の [MicroLink](https://github.com/CamM2325/microlink)（MIT ライセンス、ESP-IDF 専用）だけなので、それを `components/microlink/` に同梱しています。

- PSRAM（N16R8・XIAO ともに 8MB）を使い、MicroLink の標準値（受信バッファ 512KB、ピア 16 台）で動かします
- 認証キーが拒否されたことは、MicroLink の状態（`ML_STATE_AUTH_FAILED`）から状態表示 LED で知らせます
- 本家の MicroLink に加えた変更は `components/microlink/VERSION` に記載しています
- tailnet のアクセス制御（ACL）は本体でも守ります（MicroLink の既定）。tailnet の ACL で許していない相手からは、本体の設定ページを開けません
- 中継（DERP）の既定の地域は東京（7）にしています。ほかの地域で使うときは `sdkconfig.defaults` の `CONFIG_ML_DERP_REGION` を変えてください
- 相手（ブローカーなど）の中継の地域が本体と違うとき（例: 米国のサーバー上の Home Assistant）は、その地域の中継にも 1 本だけ追加で接続して送ります（2.7.0 から。本家の MicroLink は自分の地域にしか接続しないため、届きませんでした）。TLS の作業領域は PSRAM に置いています（2.7.0 から。ESP-IDF の既定の内蔵 RAM では空きが足りないため）。PSRAM の空きが 96KB 未満のときは、追加の接続はしません。60 秒使わなければ切ります
- MicroLink は公式のクライアントではないため、Tailscale 側の仕様変更で動かなくなる可能性があります

## ライセンス

このプロジェクトのソース（`main/`、`web/index.html`、`tools/` など）は [MIT ライセンス](LICENSE) です。

同梱している MicroLink（MIT、改変あり）、wireguard-lwip（BSD 3-Clause）、ESP Web Tools（Apache-2.0）、mDNS（Apache-2.0）、QR Code Generator（MIT）と、ファームウェアに組み込まれる ESP-IDF などは、それぞれのライセンスに従います。一覧と著作権表示は [THIRD_PARTY_NOTICES.md](THIRD_PARTY_NOTICES.md) にまとめています。配布しているファームウェアにもこれらが含まれるため、設定ページの下部からも同じ内容を見られるようにしています。

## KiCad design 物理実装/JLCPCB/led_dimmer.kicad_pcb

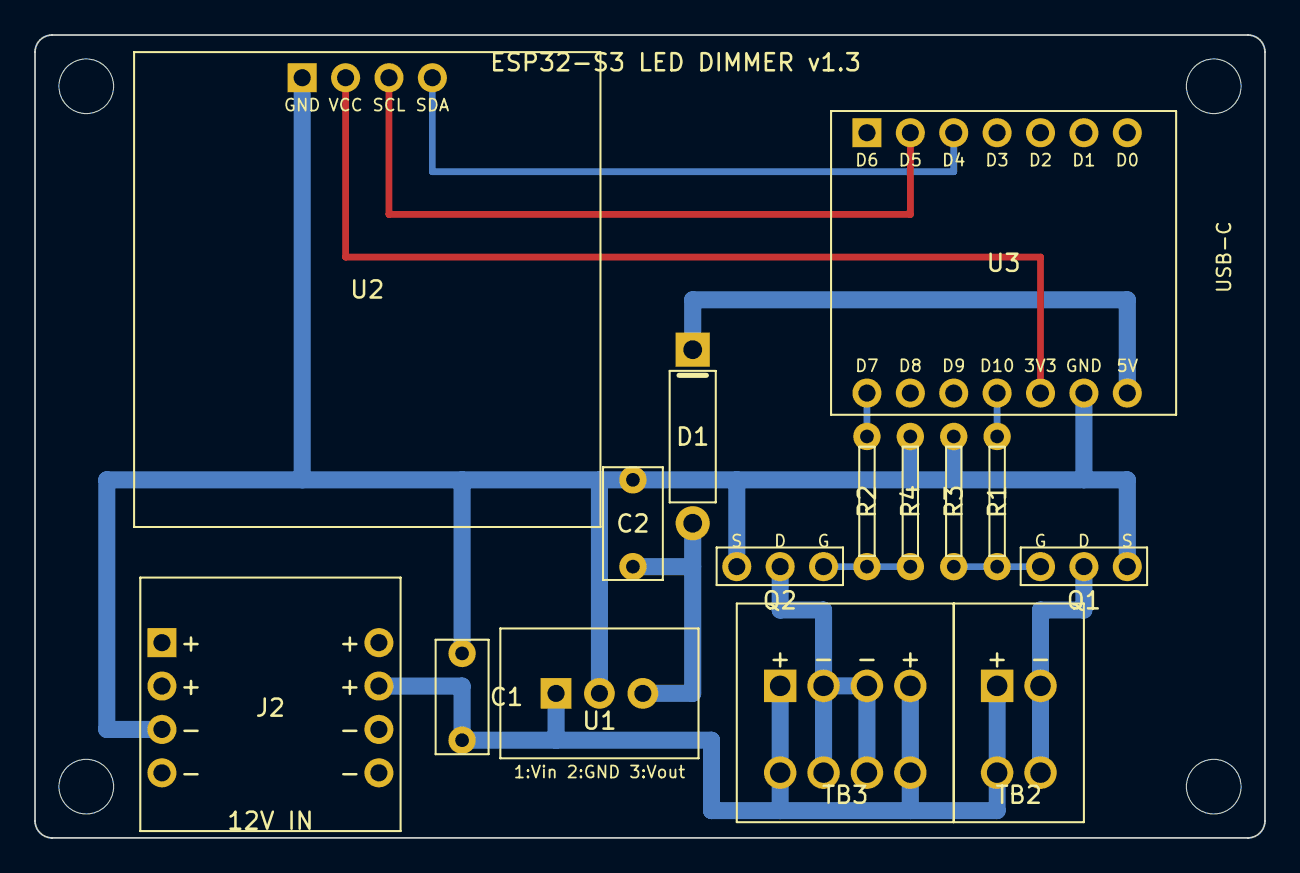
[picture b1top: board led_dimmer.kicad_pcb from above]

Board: 2 copper layers, 72.0 x 47.0 mm, 19 parts (0 on the bottom side), 13 nets.

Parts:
C1: 22uF_25V; C1
C2: 22uF; C2
D1: 1N5819; D1
H1, H2, H3, H4: M3; MountingHole_3.2mm
J2: DC_JACK_DIP; J2
Q1: 2SK4017; Q1
Q2: 2SK4017; Q2
R1: 100; R1
R2: 100; R2
R3: 100k; R3
R4: 100k; R4
TB2: LED1; TB2
TB3: LED2/3; TB3
U1: M78AR05-1; U1
U2: OLED_0.96_I2C; U2
U3: XIAO_ESP32S3; U3

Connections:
+3V3: U2.2, U3.12
+5V_XIAO: D1.1, U3.14
+12V: C1.2, J2.1, J2.2, J2.5, J2.6, TB2.1, TB2.2, TB3.1, TB3.2, TB3.7, TB3.8, U1.1
GATE1: Q1.1, R1.2, R3.2
GATE2: Q2.3, R2.2, R4.2
GND: C1.1, C2.1, J2.3, J2.4, J2.7, J2.8, Q1.3, Q2.1, R3.1, R4.1, U1.2, U2.1, U3.13
LED1-: Q1.2, TB2.3, TB2.4
LED1_PWM: R1.1, U3.11
LED23-: Q2.2, TB3.3, TB3.4, TB3.5, TB3.6
LED23_PWM: R2.1, U3.8
SCL: U2.3, U3.2
SDA: U2.4, U3.3
VDC5: C2.2, D1.2, U1.3

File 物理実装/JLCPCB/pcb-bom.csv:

記号,部品,仕様・型番,数量,備考
U3,マイコンボード,Seeed Studio XIAO ESP32S3,1,USB-Cを基板右端に向ける
—,ピンソケット,1×7 2.54mmピッチ,2,XIAO用
U2,OLEDモジュール,GME12864-52（0.96インチ I2C 4ピン）,1,アドレス0x3C／ピン順を要確認
—,ピンソケット,1×4 2.54mmピッチ,1,OLED用（浮かせて実装）
J2,DCジャックDIP化キット 完成品,AE-DC-POWER-JACK-DIP（2.1mm標準 20V 3A）,1,秋月 114610／差込口を下端へ（左右各列の上2本＋・下2本−）
U1,降圧DCDCコンバータ,M78AR05-1（MORNSUN 5V 1A 3端子）,1,1=+Vin 2=GND 3=+Vout
"Q1, Q2",Nch MOSFET,2SK4017,2,G・D・S
D1,ショットキーダイオード,1N5819,1,
"R1, R2",抵抗,100Ω 1/4W,2,茶・黒・茶・金
"R3, R4",抵抗,100kΩ 1/4W,2,茶・黒・黄・金
C1,積層セラミックコンデンサ,22µF 25V 5mmピッチ,1,
C2,積層セラミックコンデンサ,22µF 16V以上 5mmピッチ,1,
TB2,ターミナルブロック,2.54mm 2P（WJ141V-2.54-02P）,1,秋月 116999／LED1用
TB3,ターミナルブロック,2.54mm 4P（WJ141V-2.54-04P）,1,秋月 117001／LED2・LED3用
PCB,プリント基板,JLCPCB製 72×47mm 2層 1.6mm,1,led_dimmer_gerber_JLCPCB.zip
—,ACアダプタ,12V 2A以上 2.1mm センタープラス,1,
—,LED（基板外）,12V 3W,3,LED1=GPIO9／LED2・LED3=GPIO44

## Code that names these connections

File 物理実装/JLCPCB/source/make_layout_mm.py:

#!/usr/bin/env python3
"""PCB layout v2 (mm). Parts keep 2.54 mm pitch within each part, but parts are placed freely.
Writes layout_mm.json consumed by gen_pcb2.py."""
import json
P = 2.54
def g(c, r):  # old perfboard grid -> mm (used for the XIAO / MOSFET / terminal block block that is unchanged)
    return [round(5.52 + (c - 1) * P, 3), round(5.72 + (r - 1) * P, 3)]

parts = []
def part(ref, typ, val, body, pins, **kw):
    d = dict(ref=ref, type=typ, val=val, body=body, pins=pins); d.update(kw); parts.append(d)
def pin(p, xy, net): return dict(p=p, x=xy[0], y=xy[1], net=net)

# XIAO (unchanged position)
top = ["D6", "D5", "D4", "D3", "D2", "D1", "D0"]; topnet = [None, "SCL", "SDA", None, None, None, None]
bot = ["D7", "D8", "D9", "D10", "3V3", "GND", "5V"]; botnet = ["G44", None, None, "G9", "V33", "GND", "V5"]
xp = [pin(top[i], g(18 + i, 1), topnet[i]) for i in range(7)] + [pin(bot[i], g(18 + i, 7), botnet[i]) for i in range(7)]
part("U3", "xiao", "XIAO_ESP32S3", [46.6, 4.45, 66.8, 22.23], xp)

# OLED 0.96" (27.3 x 27.8), header 4 pins at top, centred
ox0, oy0 = 5.8, 1.0   # clear of the top-left M3 hole (screw head r=2.75)
pc = ox0 + 27.3 / 2
oy = 2.5
ol = [pin(n, [round(pc + (i - 1.5) * P, 3), oy], net) for i, (n, net) in enumerate([("GND", "GND"), ("VCC", "V33"), ("SCL", "SCL"), ("SDA", "SDA")])]
part("U2", "oled", "OLED_0.96_I2C", [ox0, oy0, ox0 + 27.3, oy0 + 27.8], ol, raised=True)

# J2 DC jack DIP module 15.24 sq, opening down at board bottom edge; 2 columns x 4 pins, 12.7 mm apart.
jx0, jy1 = 8.0 - 2.54 + 0.7, 47.0   # 3.16 mm from the M3 hole centre (head r=2.75)
jy0 = jy1 - 15.24
colx = [jx0 + 1.27, jx0 + 1.27 + 12.7]
rowy = [round(jy0 + 3.81 + k * P, 3) for k in range(4)]
jp = []
for cx in colx:
    for k, y in enumerate(rowy):
        jp.append(pin("+" if k < 2 else "-", [round(cx, 3), y], "V12" if k < 2 else "GND"))
part("J2", "jack", "DC_JACK_DIP", [jx0, jy0, jx0 + 15.24, jy1], jp)

# U1 M78AR05-1 horizontal, pins y=38.54
ux = [30.5, 33.04, 35.58]
part("U1", "sip", "M78AR05-1", [27.24, 34.74, 38.84, 42.34],
     [pin("1", [ux[0], 38.54], "V12"), pin("2", [ux[1], 38.54], "GND"), pin("3", [ux[2], 38.54], "VDC5")])

# D1 vertical, K top (bridges the GND bus)
part("D1", "diode", "1N5819", [37.15, 19.66, 39.85, 27.36], [pin("K", [38.5, 18.42], "V5"), pin("A", [38.5, 28.58], "VDC5")], low=True)
# C2 output cap (5.08 mm), GND pad on the bus
part("C2", "ccap", "22uF", [33.25, 25.3, 36.75, 31.9], [pin("2", [35.0, 26.04], "GND"), pin("1", [35.0, 31.12], "VDC5")], low=True)
# C1 input cap (5.08 mm)
part("C1", "ccap", "22uF_25V", [23.45, 35.4, 26.55, 42.1], [pin("-", [25.0, 36.2], "GND"), pin("+", [25.0, 41.28], "V12")], low=True)

# Cells / MOSFETs / terminal blocks (unchanged)
part("R1", "res", "100", [55.87, 24.1, 56.77, 30.5], [pin("1", g(21, 8), "G9"), pin("2", g(21, 11), "GATE1")], low=True)
part("R3", "res", "100k", [53.33, 24.1, 54.23, 30.5], [pin("1", g(20, 8), "GND"), pin("2", g(20, 11), "GATE1")], low=True)
part("R2", "res", "100", [48.25, 24.1, 49.15, 30.5], [pin("1", g(18, 8), "G44"), pin("2", g(18, 11), "GATE2")], low=True)
part("R4", "res", "100k", [50.79, 24.1, 51.69, 30.5], [pin("1", g(19, 8), "GND"), pin("2", g(19, 11), "GATE2")], low=True)
part("Q1", "fet", "2SK4017", [57.7, 30.0, 65.1, 32.2], [pin("G", g(22, 11), "GATE1"), pin("D", g(23, 11), "LED1N"), pin("S", g(24, 11), "GND")])
part("Q2", "fet", "2SK4017", [39.9, 30.0, 47.3, 32.2], [pin("S", g(15, 11), "GND"), pin("D", g(16, 11), "LED2N"), pin("G", g(17, 11), "GATE2")])
# WJ141V: 2 pins per pole, 5.08 mm apart; body 12.8 deep, 2.9 mm from the lower pin row to the body edge
TU, TL = 38.10, 43.18
def tbpins(cols, nets):
    out = []
    for c, (lab, net) in zip(cols, nets):
        x = g(c, 1)[0]
        out += [pin(lab, [x, TU], net), pin(lab, [x, TL], net)]
    return out
part("TB3", "tb", "LED2/3", [41.08, TL - 9.9, 53.78, TL + 2.9], tbpins([16, 17, 18, 19], [("+", "V12"), ("-", "LED2N"), ("-", "LED2N"), ("+", "V12")]))
part("TB2", "tb", "LED1", [53.78, TL - 9.9, 61.4, TL + 2.9], tbpins([21, 22], [("+", "V12"), ("-", "LED1N")]))

B, F = "B.Cu", "F.Cu"
wires = []
def w(net, layer, pts, note): wires.append(dict(net=net, layer=layer, pts=pts, to=note))
# GND
w("GND", B, [[4.2, 40.65], [4.2, 26.04], [63.94, 26.04]], "J2(-) -> GND bus y=26.04")
w("GND", B, [[4.2, 40.65], [colx[0], 40.65]], "J2(-) left column")
w("GND", B, [[ol[0]["x"], 2.5], [ol[0]["x"], 26.04]], "OLED GND -> bus")
w("GND", B, [g(23, 7), [g(23, 7)[0], 26.04]], "XIAO GND -> bus")
w("GND", B, [g(24, 11), [g(24, 11)[0], 26.04]], "Q1 S -> bus")
w("GND", B, [g(15, 11), [g(15, 11)[0], 26.04]], "Q2 S -> bus")
w("GND", B, [g(19, 8), [g(19, 8)[0], 26.04]], "R4 -> bus")
w("GND", B, [g(20, 8), [g(20, 8)[0], 26.04]], "R3 -> bus")
w("GND", B, [[33.04, 38.54], [33.04, 26.04]], "U1 GND -> bus")
w("GND", B, [[25.0, 36.2], [25.0, 26.04]], "C1(-) -> bus")
# +12V
w("V12", B, [[colx[1], rowy[1]], [25.0, rowy[1]], [25.0, 41.28], [39.6, 41.28], [39.6, 45.4], [g(21, 1)[0], 45.4]], "J2(+) -> C1(+) -> 12V bus (y=41.28 / 45.4)")
w("V12", B, [[30.5, 38.54], [30.5, 41.28]], "U1 Vin -> bus")
for c in (16, 19, 21):
    w("V12", B, [[g(c, 1)[0], TU], [g(c, 1)[0], TL], [g(c, 1)[0], 45.4]], "TB+ (both pins) -> bus")
for c, n in ((17, "LED2N"), (18, "LED2N"), (22, "LED1N")):
    w(n, B, [[g(c, 1)[0], TU], [g(c, 1)[0], TL]], "TB- pin pair")
# DCDC out / 5V
w("VDC5", B, [[35.58, 38.54], [38.5, 38.54], [38.5, 28.58]], "U1 Vout -> D1 A")
w("VDC5", B, [[35.0, 31.12], [38.5, 31.12]], "C2 -> D1 A")
w("V5", B, [[38.5, 18.42], [38.5, 15.5], [g(24, 7)[0], 15.5], g(24, 7)], "D1 K -> XIAO 5V")
# OLED
w("V33", F, [g(22, 7), [g(22, 7)[0], 13.0], [ol[1]["x"], 13.0], [ol[1]["x"], 2.5]], "XIAO 3V3 -> OLED VCC (top)")
w("SCL", F, [g(19, 1), [g(19, 1)[0], 10.5], [ol[2]["x"], 10.5], [ol[2]["x"], 2.5]], "XIAO D5 -> OLED SCL (top)")
w("SDA", B, [g(20, 1), [g(20, 1)[0], 8.0], [ol[3]["x"], 8.0], [ol[3]["x"], 2.5]], "XIAO D4 -> OLED SDA")
# gates / LEDs
w("G44", B, [g(18, 7), g(18, 8)], "XIAO D7 -> R2")
w("G9", B, [g(21, 7), g(21, 8)], "XIAO D10 -> R1")
w("GATE1", B, [g(20, 11), g(21, 11), g(22, 11)], "R3,R1 -> Q1 G")
w("GATE2", B, [g(19, 11), g(18, 11), g(17, 11)], "R4,R2 -> Q2 G")
w("LED1N", B, [g(23, 11), g(23, 12), g(22, 12), [g(22, 1)[0], TU]], "Q1 D -> TB2-")
w("LED2N", B, [g(16, 11), g(16, 12), g(17, 12), [g(17, 1)[0], TU], [g(18, 1)[0], TU]], "Q2 D -> TB3-")

json.dump(dict(board=[72.0, 47.0], mount=[[3, 3], [69, 3], [3, 44], [69, 44]], parts=parts, wires=wires),
          open("layout_mm.json", "w"), ensure_ascii=False, indent=1)
print(len(parts), "parts", len(wires), "wires")
